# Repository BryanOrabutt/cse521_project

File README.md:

# cse521_project

ESP32 code for the project is located in espressif_code/pet-feeder/main. To build the ESP32 code first get the ESP-IDF following these instructions https://docs.espressif.com/projects/esp-idf/en/v3.3/get-started/index.html. Then simply enter the pet-feeder directory and run `make menuconfig` and configure your programmer and WiFi SSID. Then run `make flash -j4` to program the device.

The directory server/src/ contains the code to run the dispense scheduler. This can also be run locally without an AWS EC2 instance. Simply install AWSIoTPythonSDK.MQTTLib with pip and run the petfeeder.py program.

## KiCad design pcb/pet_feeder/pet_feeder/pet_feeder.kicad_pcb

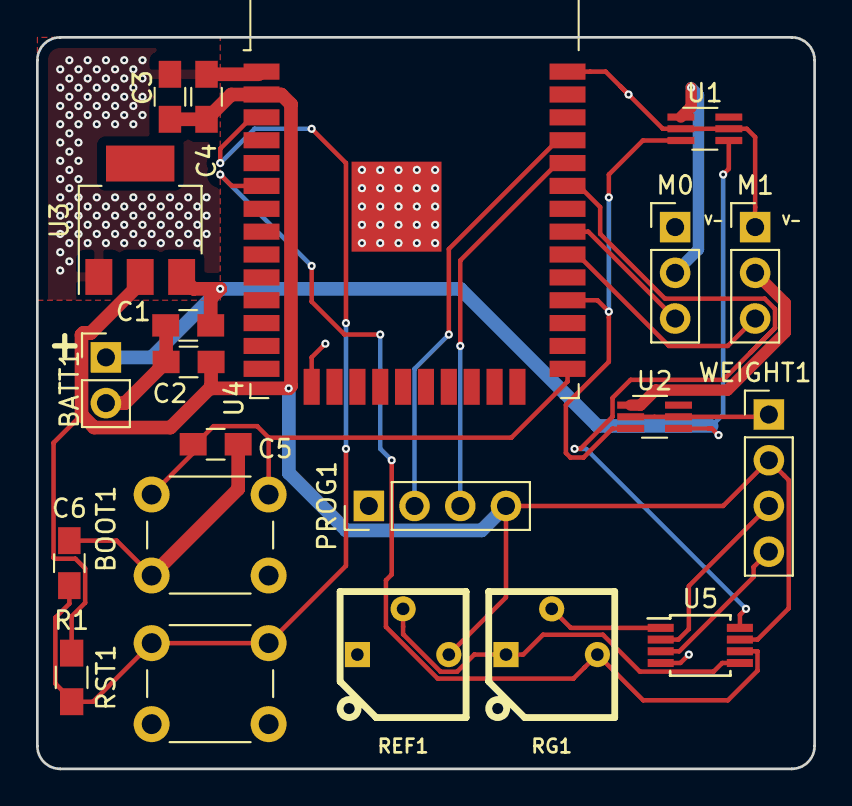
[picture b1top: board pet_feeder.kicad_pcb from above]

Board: 2 copper layers, 43.2 x 40.6 mm, 21 parts (0 on the bottom side), 18 nets.

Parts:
BATT1: BATT; Pin_Header_Straight_1x02_Pitch2.54mm
BOOT1: BOOT; SW_PUSH_6mm
C1, C2: 4.7u; C_0805_HandSoldering
C3, C5, C6: 100n; C_0805_HandSoldering
C4: 22u; C_0805_HandSoldering
M0: M0; Pin_Header_Straight_1x03_Pitch2.54mm
M1: M1; Pin_Header_Straight_1x03_Pitch2.54mm
PROG1: PROG; Pin_Header_Straight_1x04_Pitch2.54mm
R1: 10K; R_0805_HandSoldering
REF1: 500K; bourns3362p
RG1: 500K; bourns3362p
RST1: RST; SW_PUSH_6mm
U1, U2: SiP32431; SOT-363_SC-70-6_Handsoldering
U3: AP7361C-33E; SOT-223-3_TabPin2
U4: ESP32-WROOM-32D; ESP32-WROOM-32
U5: INA322; MSOP-8_3x3mm_Pitch0.65mm
WEIGHT1: WEIGHT; Pin_Header_Straight_1x04_Pitch2.54mm

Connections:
+3V3: C2.1, C3.2, C4.2, PROG1.4, R1.2, REF1.3, U3.2, U4.2, U5.7, WEIGHT1.2
+BATT: BATT1.1, C1.1, U1.4, U2.4, U3.3
-BATT: BATT1.2, BOOT1.2, C1.2, C2.2, C3.1, C4.1, C5.2, C6.2, M0.1, M1.1, PROG1.1, REF1.1, RST1.2, U1.2, U1.5, U2.2, U2.5, U3.1, U4.1, U4.15, U4.38, U4.39, U5.4, WEIGHT1.1
/GPIO0: BOOT1.1, C5.1, U4.25
/REF: REF1.2, RG1.1, U5.5
/RG: RG1.2, U5.1
/RST: C6.1, R1.1, RST1.1, U4.3
/RX: PROG1.3, U4.34
/SRV0_PWM: M0.3, U4.31
/SRV1_PWM: M1.3, U4.30
/SRV1_PWR: M1.2, U2.1
/SRV_EN: U1.3, U2.3, U4.28
/SRV_PWR: M0.2, U1.1
/TX: PROG1.2, U4.35
/WS+: U5.3, WEIGHT1.4
/WS-: U5.2, WEIGHT1.3
/WS_ADC: RG1.3, U4.6, U5.6
/~WS_EN: U4.33, U5.8

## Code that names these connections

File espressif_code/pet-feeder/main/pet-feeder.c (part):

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#define NOP() asm volatile ("nop")
#define WS_BASELINE 1077
#define WS_GRAMS_PER_COUNT 0.0485608
#define WS_EN 21
#define WS_ADC 34
#define SRV_EN 17
#define AMP_EN 22
#define SRV0 18
#define SRV1 19
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        if(time_dispense)
        {
            ESP_LOGI(TAG, "Dispensing %d grams of food", dispense_amount);
            gpio_set_level(SRV_EN, 1);
            
            for (count = 0; count < SERVO_MAX_DEGREE-39; count+=5) 
            {
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            time_dispense = 0;
            tx_queue_empty = 0;
            xQueueSend(tx_queue, (void*)&id, (TickType_t)0);
            gpio_set_level(SRV_EN, 0);
        }
        
        vTaskSuspend(0);
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    {
        if(sample_weight)
        {
            gpio_set_level(WS_EN, 0);
            reading = 0;
            sample_weight = 0;
            
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            
            reading /= 64;
            weight = ((float)(reading-WS_BASELINE))*WS_GRAMS_PER_COUNT;
            gpio_set_level(WS_EN, 1);
            sample_weight = 0;
            tx_queue_empty = 0;
            xQueueSend(tx_queue, (void*)&id, (TickType_t)0);        
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    //set as output mode
    io_conf.mode = GPIO_MODE_OUTPUT;
    //bit mask of the pins that you want to set,
    io_conf.pin_bit_mask = (1ULL<<WS_EN | 1ULL<<SRV_EN);
    //disable pull-down mode
    io_conf.pull_down_en = 0;
    //disable pull-up mode
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    io_conf.pull_down_en = 1;
    gpio_config(&io_conf);
    
    gpio_set_level(WS_EN, 1);
    gpio_set_level(SRV_EN, 0);

    
    //create a queue to handle gpio event from isr
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    gpio_isr_handler_add(MOTION, motion_isr, (void*) MOTION);
    
    esp_sleep_enable_timer_wakeup(5000000); //wakeup every 5 seconds;
    rtc_gpio_pullup_en(SRV_EN);
    rtc_gpio_pulldown_en(MOTION);
    esp_sleep_enable_ext1_wakeup(GPIO_NUM_4, ESP_EXT1_WAKEUP_ANY_HIGH);
    rtc_gpio_isolate(GPIO_NUM_12);
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
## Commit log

2019-09-08 Started project repo
2019-09-08 Add .gitignore
2019-09-08 Reorganize code
2019-09-08 Update gitignore for tex
2019-09-08 Add tex files
2019-09-08 Wifi powersave working.
2019-09-09 local update
2019-09-11 Update proposal slides + report
2019-09-12 update proposal
2019-09-12 update on proposal
2019-09-12 Servo example working. Deep and light sleeps work. Need to do AWS
2019-09-18 update
    add object detection
2019-09-18 add face_detecttion
    prototype
2019-09-19 Update gitignore
2019-09-19 Modified example allowing AWS servo control working
2019-09-30 Bug in using xQueues to receive data... ESP and AWS can hear themselves talk
2019-10-01 JSON parsing seems to be working
2019-10-02 JSON builder working and functions to handle requests put into place
2019-10-12 Update JSON parsing to handling request array. Change publish loop frequency
2019-10-16 Load cell sensor not working. Need to fix timing issues
2019-10-17 update on cat face detection
    cat face detection is now working
2019-10-17 update
    some update
2019-10-19 Changed mcpwm for ledc for increased timer resolution
2019-10-19 Changed count to local var instead of global volatile var
2019-10-20 Fixed servo jitter issue
2019-10-29 Working on weight sensor code
2019-10-29 Adding pcb files
2019-10-29 Force commiting kicad .lib files
2019-10-30 Board revision 2 done
2019-10-30 Fixed gerber archive
2019-10-31 Weight sensor code in place
2019-11-05 Motion sensor working
2019-11-08 Add server side code
2019-11-21 Fix server crashing from race condition. Fix dispense mode torque
2019-12-11 Add final code

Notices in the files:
espressif_code/pet-feeder/main/pet-feeder.c:
Copyright 2010-2015 Amazon.com, Inc. or its affiliates. All Rights Reserved.
Additions Copyright 2016 Espressif Systems (Shanghai) PTE LTD
Licensed under the Apache License, Version 2.0 (the "License").
